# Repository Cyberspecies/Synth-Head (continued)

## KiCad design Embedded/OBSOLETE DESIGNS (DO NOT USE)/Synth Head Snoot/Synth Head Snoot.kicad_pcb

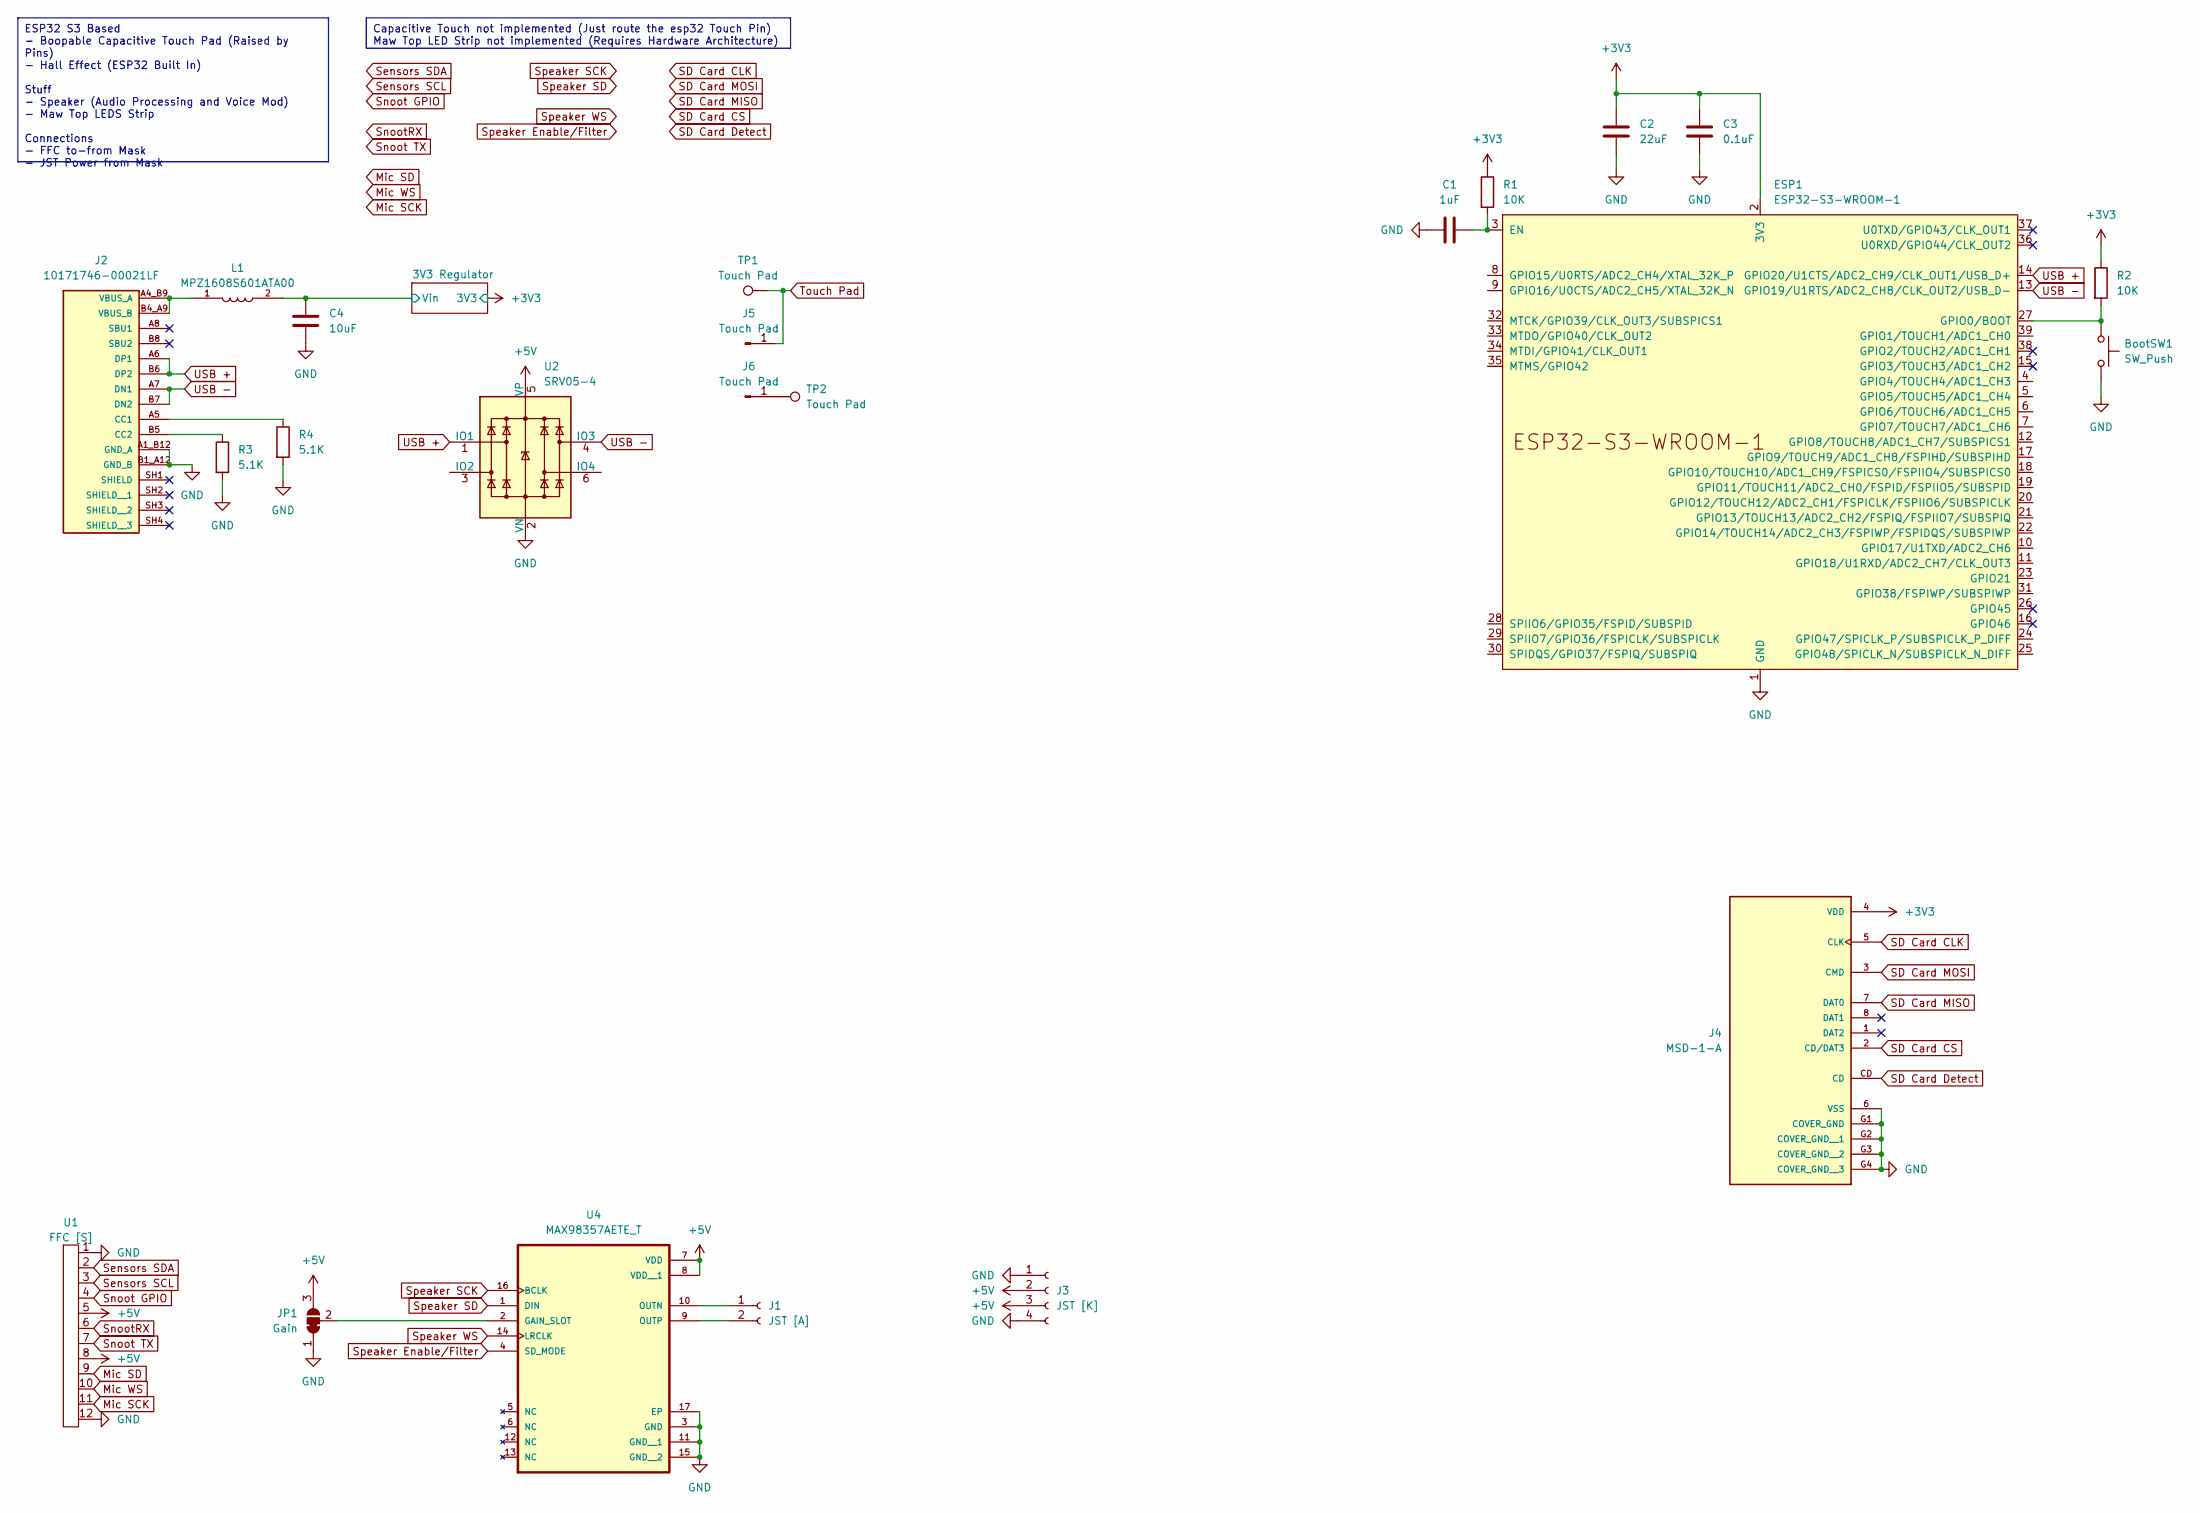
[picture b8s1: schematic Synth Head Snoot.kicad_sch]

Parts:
BootSW1: SW_Push; Button-R-667843
C1: 1uF; C_0603_1608Metric
C2: 22uF; C_0603_1608Metric_Pad1.08x0.95mm_HandSolder
C3: 0.1uF; C_0603_1608Metric_Pad1.08x0.95mm_HandSolder
C4: 10uF; C_0603_1608Metric
ESP1: ESP32-S3-WROOM-1; ESP32-S3-WROOM-1U
J1: JST [A]; Molex_PicoBlade_53048-0210_1x02_P1.25mm_Horizontal
J2: 10171746-00021LF; AMPHENOL_10171746-00021LF; PARTREV A
J3: JST [K]; Molex_PicoBlade_53048-0410_1x04_P1.25mm_Horizontal
J4: MSD-1-A; CUI_MSD-1-A; PARTREV 1.0
J5, J6: Touch Pad; PinHeader_1x01_P2.54mm_Vertical
JP1: Gain; SolderJumper-3_P1.3mm_Bridged12_Pad1.0x1.5mm_NumberLabels
L1: MPZ1608S601ATA00; INDC1608X95N
R1, R2: 10K; R_0603_1608Metric
R3, R4: 5.1K; R_0603_1608Metric
TP1, TP2: Touch Pad; TestPoint_Pad_D2.0mm
U1: FFC [S]; FFC Aliexpress 0.5mm 12P
U2: SRV05-4; SOT-23-6
U4: MAX98357AETE_T; QFN50P300X300X80-17N

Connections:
+3V3: C2.1, C3.1, ESP1.2 (3V3), J4.4 (VDD), R1.1, R2.1; also elsewhere on the board
+5V: J3.2, J3.3, JP1.3 (B), U1.5, U1.8, U2.5 (VP), U4.7 (VDD), U4.8 (VDD__1)
/3V3 Regulator/Vin: C4.1, L1.2; also elsewhere on the board
GND: BootSW1.2, C1.1, C2.2, C3.2, C4.2, ESP1.1 (GND), ESP1.40 (GND), ESP1.41 (GND), J2.A1_B12 (GND_A), J2.B1_A12 (GND_B), J3.1, J3.4, J4.6 (VSS), J4.G1 (COVER_GND), J4.G2 (COVER_GND__1), J4.G3 (COVER_GND__2), J4.G4 (COVER_GND__3), JP1.1 (A), R3.2, R4.2, U1.1, U1.12, U2.2 (VN), U4.3 (GND), U4.11 (GND__1), U4.15 (GND__2), U4.17 (EP); also elsewhere on the board
Mic SCK: U1.11
Mic SD: U1.9
Mic WS: U1.10
unnamed: C1.2, ESP1.3 (EN), R1.2
unnamed: BootSW1.1, ESP1.27 (GPIO0/BOOT), R2.2
unnamed: J1.1, U4.10 (OUTN)
unnamed: J1.2, U4.9 (OUTP)
unnamed: J2.A5 (CC1), R4.1
unnamed: J2.B5 (CC2), R3.1
unnamed: J2.A4_B9 (VBUS_A), J2.B4_A9 (VBUS_B), L1.1
unnamed: J6.1, TP2.1
unnamed: JP1.2 (C), U4.2 (GAIN_SLOT)
SD Card CLK: J4.5 (CLK)
SD Card CS: J4.2 (CD/DAT3)
SD Card Detect: J4.CD
SD Card MISO: J4.7 (DAT0)
SD Card MOSI: J4.3 (CMD)
Sensors SCL: U1.3
Sensors SDA: U1.2
Snoot GPIO: U1.4
Snoot TX: U1.7
SnootRX: U1.6
Speaker Enable/Filter: U4.4 (SD_MODE)
Speaker SCK: U4.16 (BCLK)
Speaker SD: U4.1 (DIN)
Speaker WS: U4.14 (LRCLK)
Touch Pad: J5.1, TP1.1
USB +: ESP1.14 (GPIO20/U1CTS/ADC2_CH9/CLK_OUT1/USB_D+), J2.A6 (DP1), J2.B6 (DP2), U2.1 (IO1)
USB -: ESP1.13 (GPIO19/U1RTS/ADC2_CH8/CLK_OUT2/USB_D-), J2.A7 (DN1), J2.B7 (DN2), U2.4 (IO3)

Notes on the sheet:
Capacitive Touch not implemented (Just route the esp32 Touch Pin) Maw Top LED Strip not implemented (Requires Hardware Architecture)
ESP32 S3 Based - Boopable Capacitive Touch Pad (Raised by Pins) - Hall Effect (ESP32 Built In) Stuff - Speaker (Audio Processing and Voice Mod) - Maw Top LEDS Strip Connections - FFC to-from Mask - JST Power from Mask

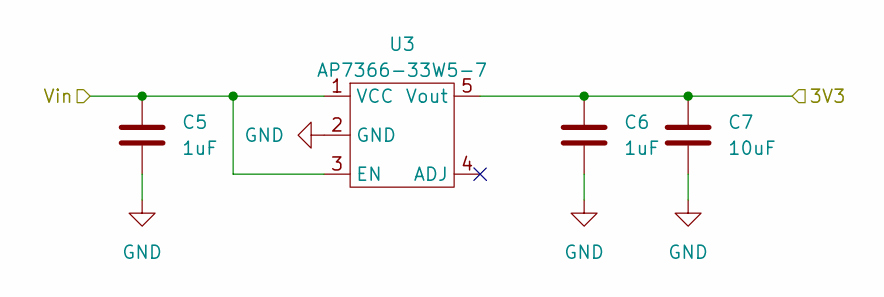
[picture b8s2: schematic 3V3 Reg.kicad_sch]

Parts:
C5, C6: 1uF; R_0603_1608Metric
C7: 10uF; C_0603_1608Metric
U3: AP7366-33W5-7; AP7366

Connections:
+3V3: C6.1, C7.1, U3.5 (Vout); also elsewhere on the board
/3V3 Regulator/Vin: C5.1, U3.1 (VCC), U3.3 (EN); also elsewhere on the board
GND: C5.2, C6.2, C7.2, U3.2 (GND); also elsewhere on the board

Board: 2 copper layers, 27 parts (3 on the bottom side), 16 nets, no tracks yet.
